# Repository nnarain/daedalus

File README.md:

# Daedalus

Daedalus is a Raspberry Pi add-on that aim's to supply the necessary components for common robotics applications such as power distribution, IO, sensors and software defined embedded logic.

The current revision (Rev A) is a Proof-of-concept and contains the following:

- A switch mode power supply taking an input of 7V - 25V (2S to 6S LiPo battery) and and output of 5V @ 6A continuous
- A 3.3V linear regulator
- On board RP2040 co-processor
- MPU-6050 IMU
- 16 GPIO (8x Pi + 8x MCU)

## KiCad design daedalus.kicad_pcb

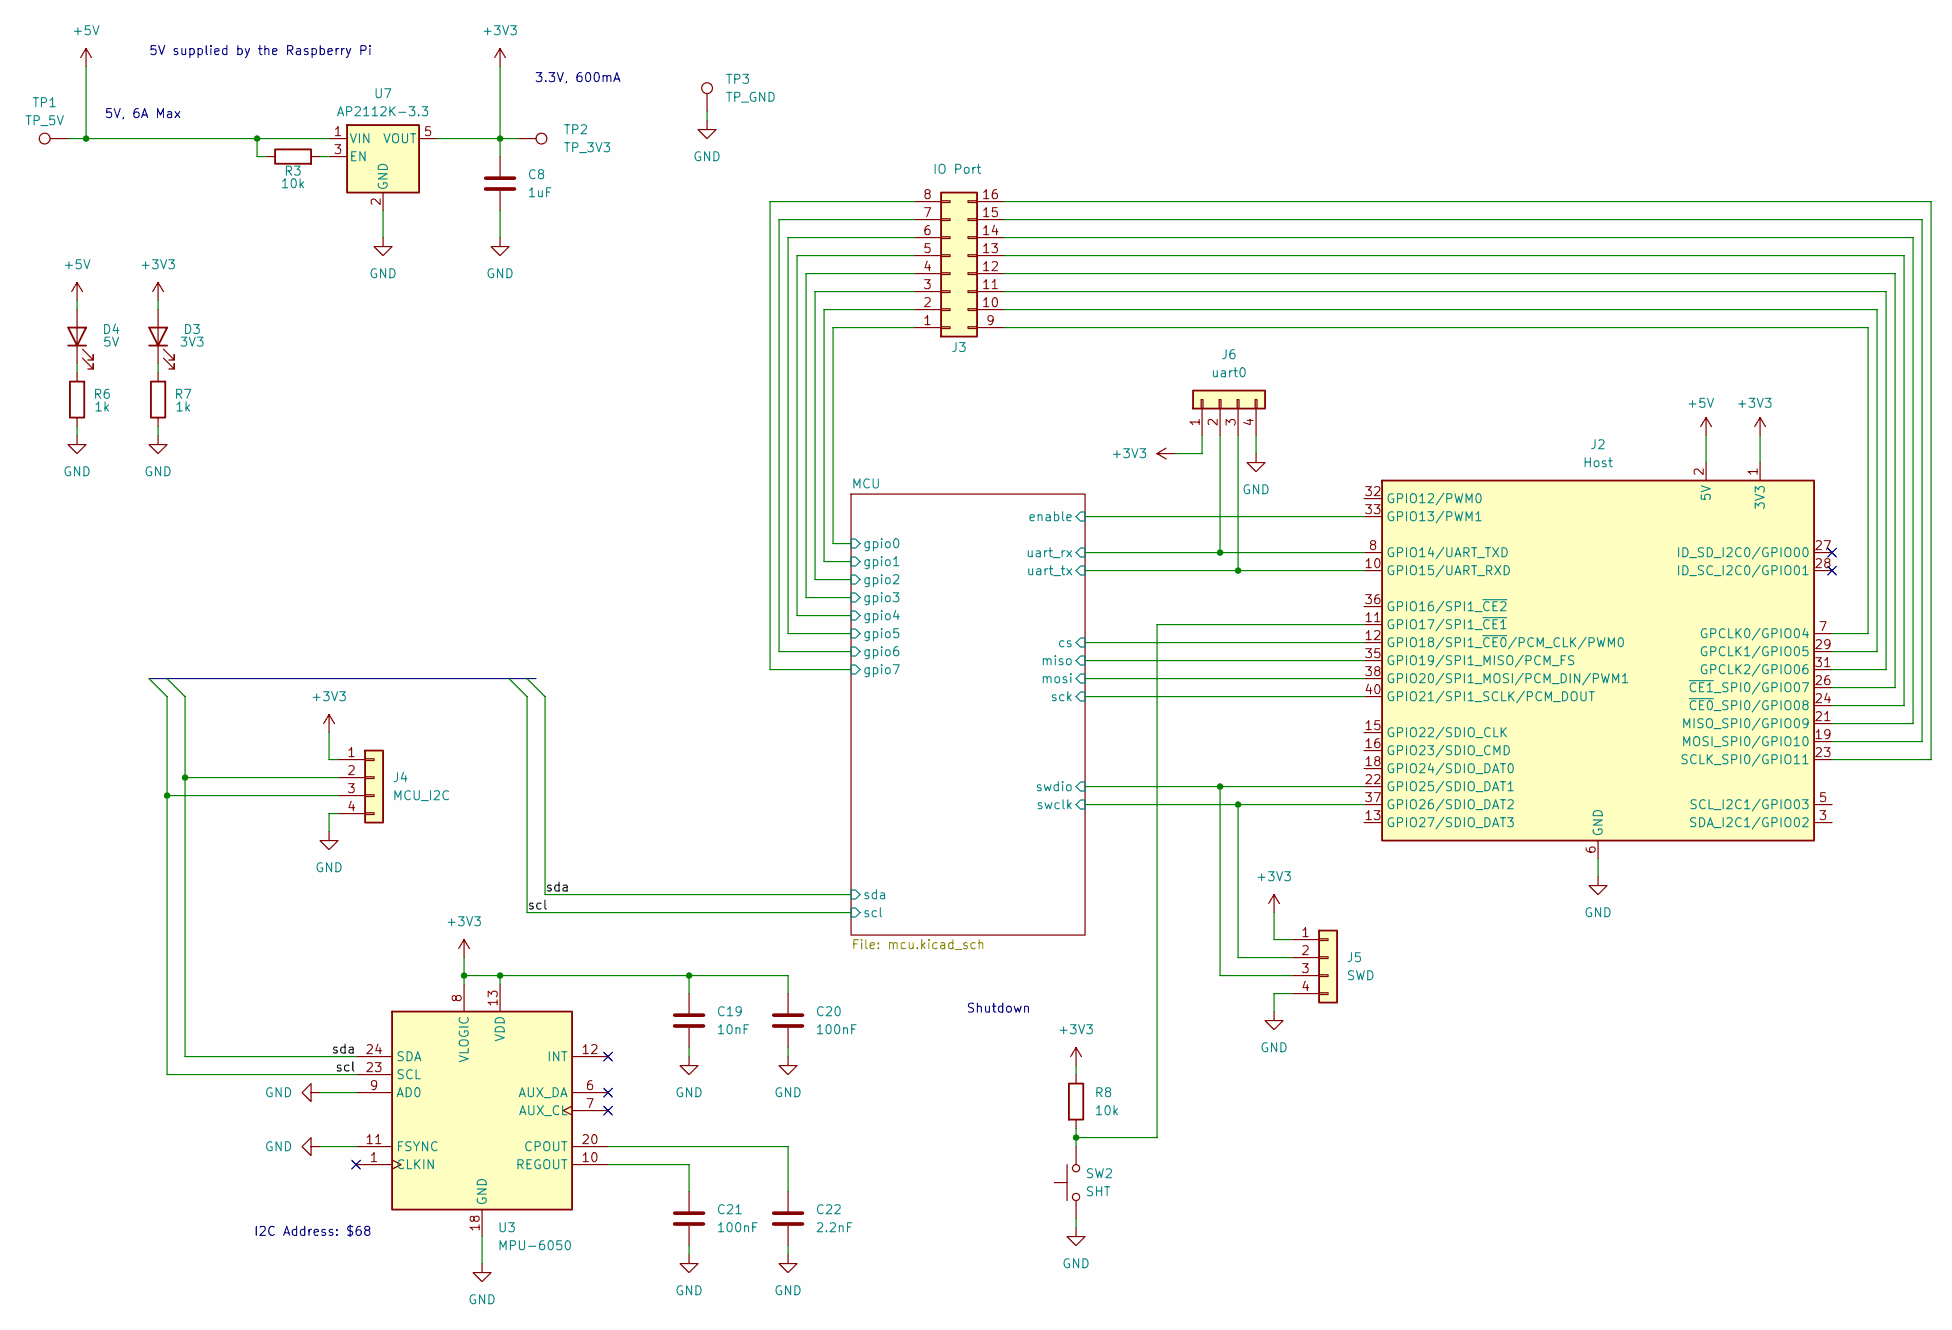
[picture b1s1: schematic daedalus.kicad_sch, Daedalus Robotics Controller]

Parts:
C8: 1uF; C_0402_1005Metric; LCSC C52923
C19: 10nF; C_0402_1005Metric; LCSC C15195
C20, C21: 100nF; C_0402_1005Metric; LCSC C307331
C22: 2.2nF; C_0402_1005Metric; LCSC C1531
D3: 3V3; LED_0603_1608Metric; LCSC C72043
D4: 5V; LED_0603_1608Metric; LCSC C72043
J2: Host; Raspberry_Pi_HAT_2_3_4
J3: IO Port; PinHeader_2x08_P2.54mm_Vertical
J4: MCU_I2C; PinHeader_1x04_P2.54mm_Vertical
J5: SWD; PinHeader_1x04_P2.54mm_Vertical
J6: uart0; PinHeader_1x04_P2.54mm_Vertical
R3, R8: 10k; R_0402_1005Metric; LCSC C25744
R6, R7: 1k; R_0402_1005Metric; LCSC C25543
SW2: SHT; TS-1088-AR02016; LCSC C720477
TP1: TP_5V; TestPoint_Pad_2.0x2.0mm
TP2: TP_3V3; TestPoint_Pad_2.0x2.0mm
TP3: TP_GND; TestPoint_Pad_2.0x2.0mm
U3: MPU-6050; InvenSense_QFN-24_4x4mm_P0.5mm; LCSC C24112
U7: AP2112K-3.3; SOT-23-5; LCSC C51118

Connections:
+3V3: C8.1, C19.1, C20.1, D3.2 (A), J2.1 (3V3), J2.17 (3V3), J4.1, J5.1, J6.1, R8.1, TP2.1, U3.8 (VLOGIC), U3.13 (VDD), U7.5 (VOUT); also elsewhere on the board
+5V: D4.2 (A), J2.2 (5V), J2.4 (5V), R3.1, TP1.1, U7.1 (VIN); also elsewhere on the board
/MCU/cs: J2.12 (GPIO18/SPI1_~CE0/PCM_CLK/PWM0); also elsewhere on the board
/MCU/gpio0: J3.1; also elsewhere on the board
/MCU/gpio1: J3.2; also elsewhere on the board
/MCU/gpio2: J3.3; also elsewhere on the board
/MCU/gpio3: J3.4; also elsewhere on the board
/MCU/gpio4: J3.5; also elsewhere on the board
/MCU/gpio5: J3.6; also elsewhere on the board
/MCU/gpio6: J3.7; also elsewhere on the board
/MCU/gpio7: J3.8; also elsewhere on the board
/MCU/miso: J2.35 (GPIO19/SPI1_MISO/PCM_FS); also elsewhere on the board
/MCU/mosi: J2.38 (GPIO20/SPI1_MOSI/PCM_DIN/PWM1); also elsewhere on the board
/MCU/run: J2.33 (GPIO13/PWM1); also elsewhere on the board
/MCU/sck: J2.40 (GPIO21/SPI1_SCLK/PCM_DOUT); also elsewhere on the board
/MCU/swclk: J2.37 (GPIO26/SDIO_DAT2), J5.2; also elsewhere on the board
/MCU/swdio: J2.22 (GPIO25/SDIO_DAT1), J5.3; also elsewhere on the board
/MCU/uart_rx: J2.8 (GPIO14/UART_TXD), J6.2; also elsewhere on the board
/MCU/uart_tx: J2.10 (GPIO15/UART_RXD), J6.3; also elsewhere on the board
/scl: J4.3, U3.23 (SCL); also elsewhere on the board
/sda: J4.2, U3.24 (SDA); also elsewhere on the board
GND: C8.2, C19.2, C20.2, C21.2, C22.2, J2.6 (GND), J2.9 (GND), J2.14 (GND), J2.20 (GND), J2.25 (GND), J2.30 (GND), J2.34 (GND), J2.39 (GND), J4.4, J5.4, J6.4, R6.1, R7.1, SW2.1, TP3.1, U3.9 (AD0), U3.11 (FSYNC), U3.18 (GND), U7.2 (GND); also elsewhere on the board
unnamed: D3.1 (K), R7.2
unnamed: D4.1 (K), R6.2
unnamed: J2.7 (GPCLK0/GPIO04), J3.9
unnamed: J2.29 (GPCLK1/GPIO05), J3.10
unnamed: J2.31 (GPCLK2/GPIO06), J3.11
unnamed: J2.11 (GPIO17/SPI1_~CE1), R8.2, SW2.2
unnamed: J2.21 (MISO_SPI0/GPIO09), J3.14
unnamed: J2.19 (MOSI_SPI0/GPIO10), J3.15
unnamed: J2.23 (SCLK_SPI0/GPIO11), J3.16
unnamed: J2.24 (~CE0_SPI0/GPIO08), J3.13
unnamed: J2.26 (~CE1_SPI0/GPIO07), J3.12
unnamed: C22.1, U3.20 (CPOUT)
unnamed: C21.1, U3.10 (REGOUT)
unnamed: R3.2, U7.3 (EN)

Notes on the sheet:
5V, 6A Max
3.3V, 600mA
Shutdown
I2C Address: $68
5V supplied by the Raspberry Pi

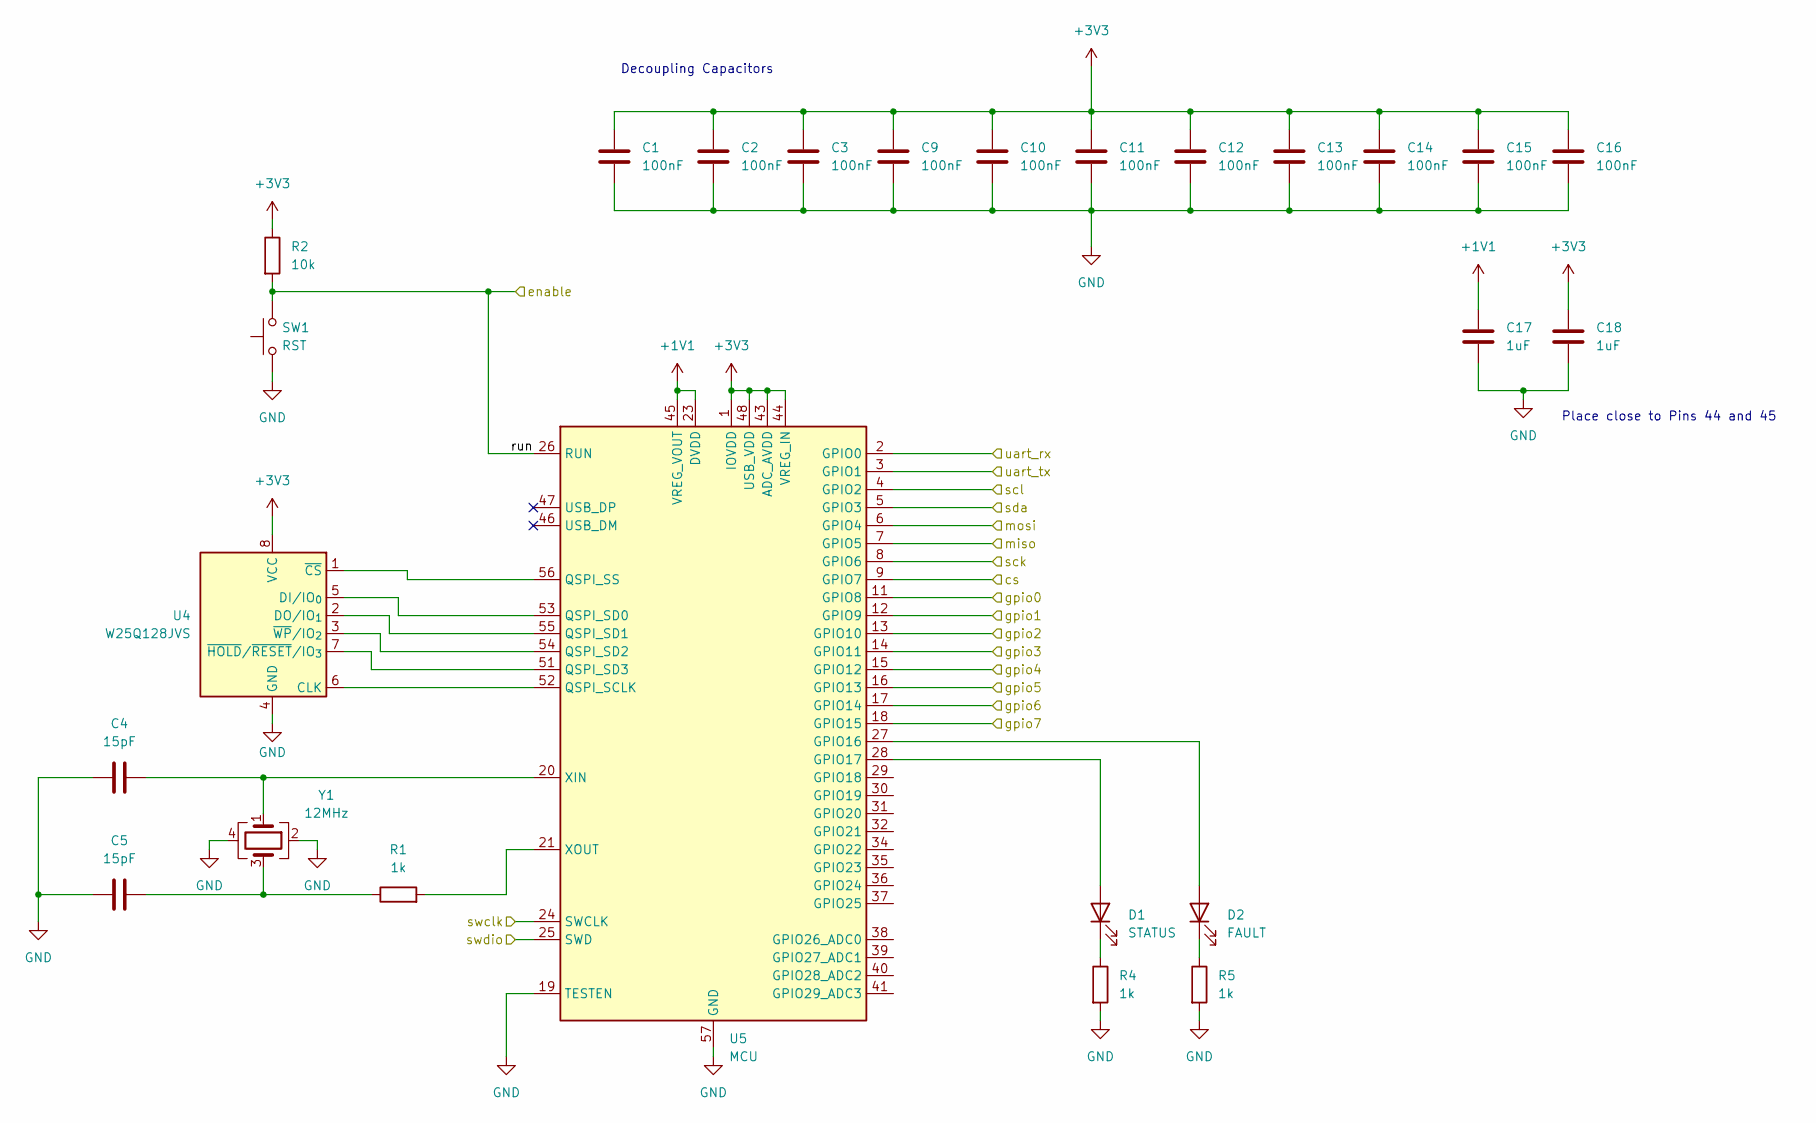
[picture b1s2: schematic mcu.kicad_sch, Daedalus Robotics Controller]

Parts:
C1, C2, C3, C9, C10, C11, C12, C13, C14, C15, C16: 100nF; C_0402_1005Metric; LCSC C307331
C4, C5: 15pF; C_0402_1005Metric; LCSC C326803
C17, C18: 1uF; C_0402_1005Metric; LCSC C52923
D1: STATUS; LED_0603_1608Metric; LCSC C72043
D2: FAULT; LED_0603_1608Metric; LCSC C2286
R1, R4, R5: 1k; R_0402_1005Metric; LCSC C25543
R2: 10k; R_0402_1005Metric; LCSC C25744
SW1: RST; TS-1088-AR02016; LCSC C720477
U4: W25Q128JVS; SOIC-8_5.3x5.3mm_P1.27mm; LCSC C97521
U5: MCU; QFN-56-1EP_7x7mm_P0.4mm_EP3.2x3.2mm; LCSC C2040
Y1: 12MHz; Crystal_SMD_3225-4Pin_3.2x2.5mm; LCSC C20625731

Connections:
+1V1: C17.2, U5.23 (DVDD), U5.45 (VREG_VOUT), U5.50 (DVDD)
+3V3: C1.2, C2.2, C3.2, C9.2, C10.2, C11.2, C12.2, C13.2, C14.2, C15.2, C16.2, C18.2, R2.1, U4.8 (VCC), U5.1 (IOVDD), U5.10 (IOVDD), U5.22 (IOVDD), U5.33 (IOVDD), U5.42 (IOVDD), U5.43 (ADC_AVDD), U5.44 (VREG_IN), U5.48 (USB_VDD), U5.49 (IOVDD); also elsewhere on the board
/MCU/cs: U5.9 (GPIO7); also elsewhere on the board
/MCU/gpio0: U5.11 (GPIO8); also elsewhere on the board
/MCU/gpio1: U5.12 (GPIO9); also elsewhere on the board
/MCU/gpio2: U5.13 (GPIO10); also elsewhere on the board
/MCU/gpio3: U5.14 (GPIO11); also elsewhere on the board
/MCU/gpio4: U5.15 (GPIO12); also elsewhere on the board
/MCU/gpio5: U5.16 (GPIO13); also elsewhere on the board
/MCU/gpio6: U5.17 (GPIO14); also elsewhere on the board
/MCU/gpio7: U5.18 (GPIO15); also elsewhere on the board
/MCU/miso: U5.7 (GPIO5); also elsewhere on the board
/MCU/mosi: U5.6 (GPIO4); also elsewhere on the board
/MCU/run: R2.2, SW1.2, U5.26 (RUN); also elsewhere on the board
/MCU/sck: U5.8 (GPIO6); also elsewhere on the board
/MCU/swclk: U5.24 (SWCLK); also elsewhere on the board
/MCU/swdio: U5.25 (SWD); also elsewhere on the board
/MCU/uart_rx: U5.2 (GPIO0); also elsewhere on the board
/MCU/uart_tx: U5.3 (GPIO1); also elsewhere on the board
/scl: U5.4 (GPIO2); also elsewhere on the board
/sda: U5.5 (GPIO3); also elsewhere on the board
GND: C1.1, C2.1, C3.1, C4.1, C5.2, C9.1, C10.1, C11.1, C12.1, C13.1, C14.1, C15.1, C16.1, C17.1, C18.1, R4.2, R5.2, SW1.1, U4.4 (GND), U5.19 (TESTEN), U5.57 (GND), Y1.2, Y1.4; also elsewhere on the board
unnamed: C5.1, R1.1, Y1.3
unnamed: D1.2 (A), U5.28 (GPIO17)
unnamed: D1.1 (K), R4.1
unnamed: D2.2 (A), U5.27 (GPIO16)
unnamed: D2.1 (K), R5.1
unnamed: U4.6 (CLK), U5.52 (QSPI_SCLK)
unnamed: U4.5 (DI/IO_{0}), U5.53 (QSPI_SD0)
unnamed: U4.2 (DO/IO_{1}), U5.55 (QSPI_SD1)
unnamed: U4.1 (~CS), U5.56 (QSPI_SS)
unnamed: U4.7 (~HOLD/~RESET/IO_{3}), U5.51 (QSPI_SD3)
unnamed: U4.3 (~WP/IO_{2}), U5.54 (QSPI_SD2)
unnamed: C4.2, U5.20 (XIN), Y1.1
unnamed: R1.2, U5.21 (XOUT)

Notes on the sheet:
Place close to Pins 44 and 45
Decoupling Capacitors

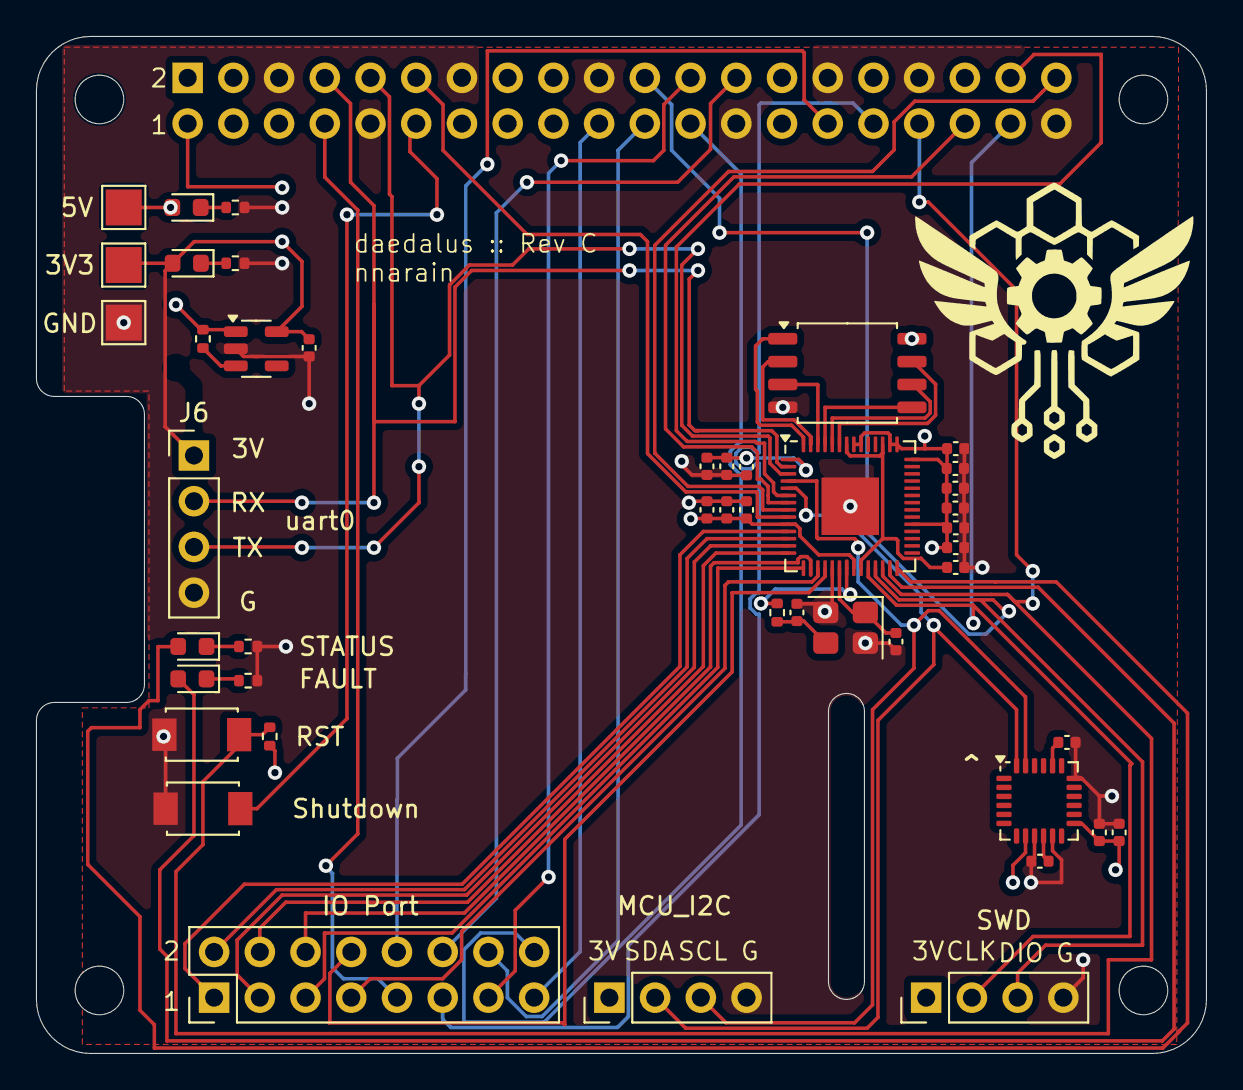
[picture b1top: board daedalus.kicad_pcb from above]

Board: 4 copper layers, 65.0 x 56.5 mm, 46 parts (0 on the bottom side), 50 nets.

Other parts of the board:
3V3: TP_3V3; TestPoint_Pad_2.0x2.0mm
5V: TP_5V; TestPoint_Pad_2.0x2.0mm
GND: TP_GND; TestPoint_Pad_2.0x2.0mm

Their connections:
+3V3: 3V3.1; also elsewhere on the board
+5V: 5V.1; also elsewhere on the board
GND: GND.1; also elsewhere on the board

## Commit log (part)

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2025-07-09 Daedalus Rev A PoC
2025-07-10 added missing lcsc part number
2025-07-10 setup ci
2025-07-12 update actions
2025-07-22 Initial plan
2025-07-22 Setup mdBook documentation structure and enable CI/CD pipeline
2025-07-22 Format type fields in book.toml for better alignment
2025-07-22 Add release and documentation badges to README
2025-07-26 cache
2025-07-26 fix raspberry pi hat pinout
2025-07-26 Complete investigation: automated revision text update solution
2025-07-26 Add quick start guide and practical examples for revision automation
2025-07-26 Add power supply test points
2025-07-26 Add automated changelog generation and 3D render to releases
2025-07-26 Complete release automation with documentation and comprehensive tests
2025-07-26 Switch to vertical xt30 connector
2025-07-27 update asset path
2025-07-27 update asset paths
2025-07-27 deploy: d8ac2846aeaa0e4a88235336f4ae31ececb95a82
2025-07-27 fix preprocessor
2025-07-27 deploy: b8275203ce818c1f368e7d2f785b13d0b7cd4fe9
2026-06-20 update kicad version
